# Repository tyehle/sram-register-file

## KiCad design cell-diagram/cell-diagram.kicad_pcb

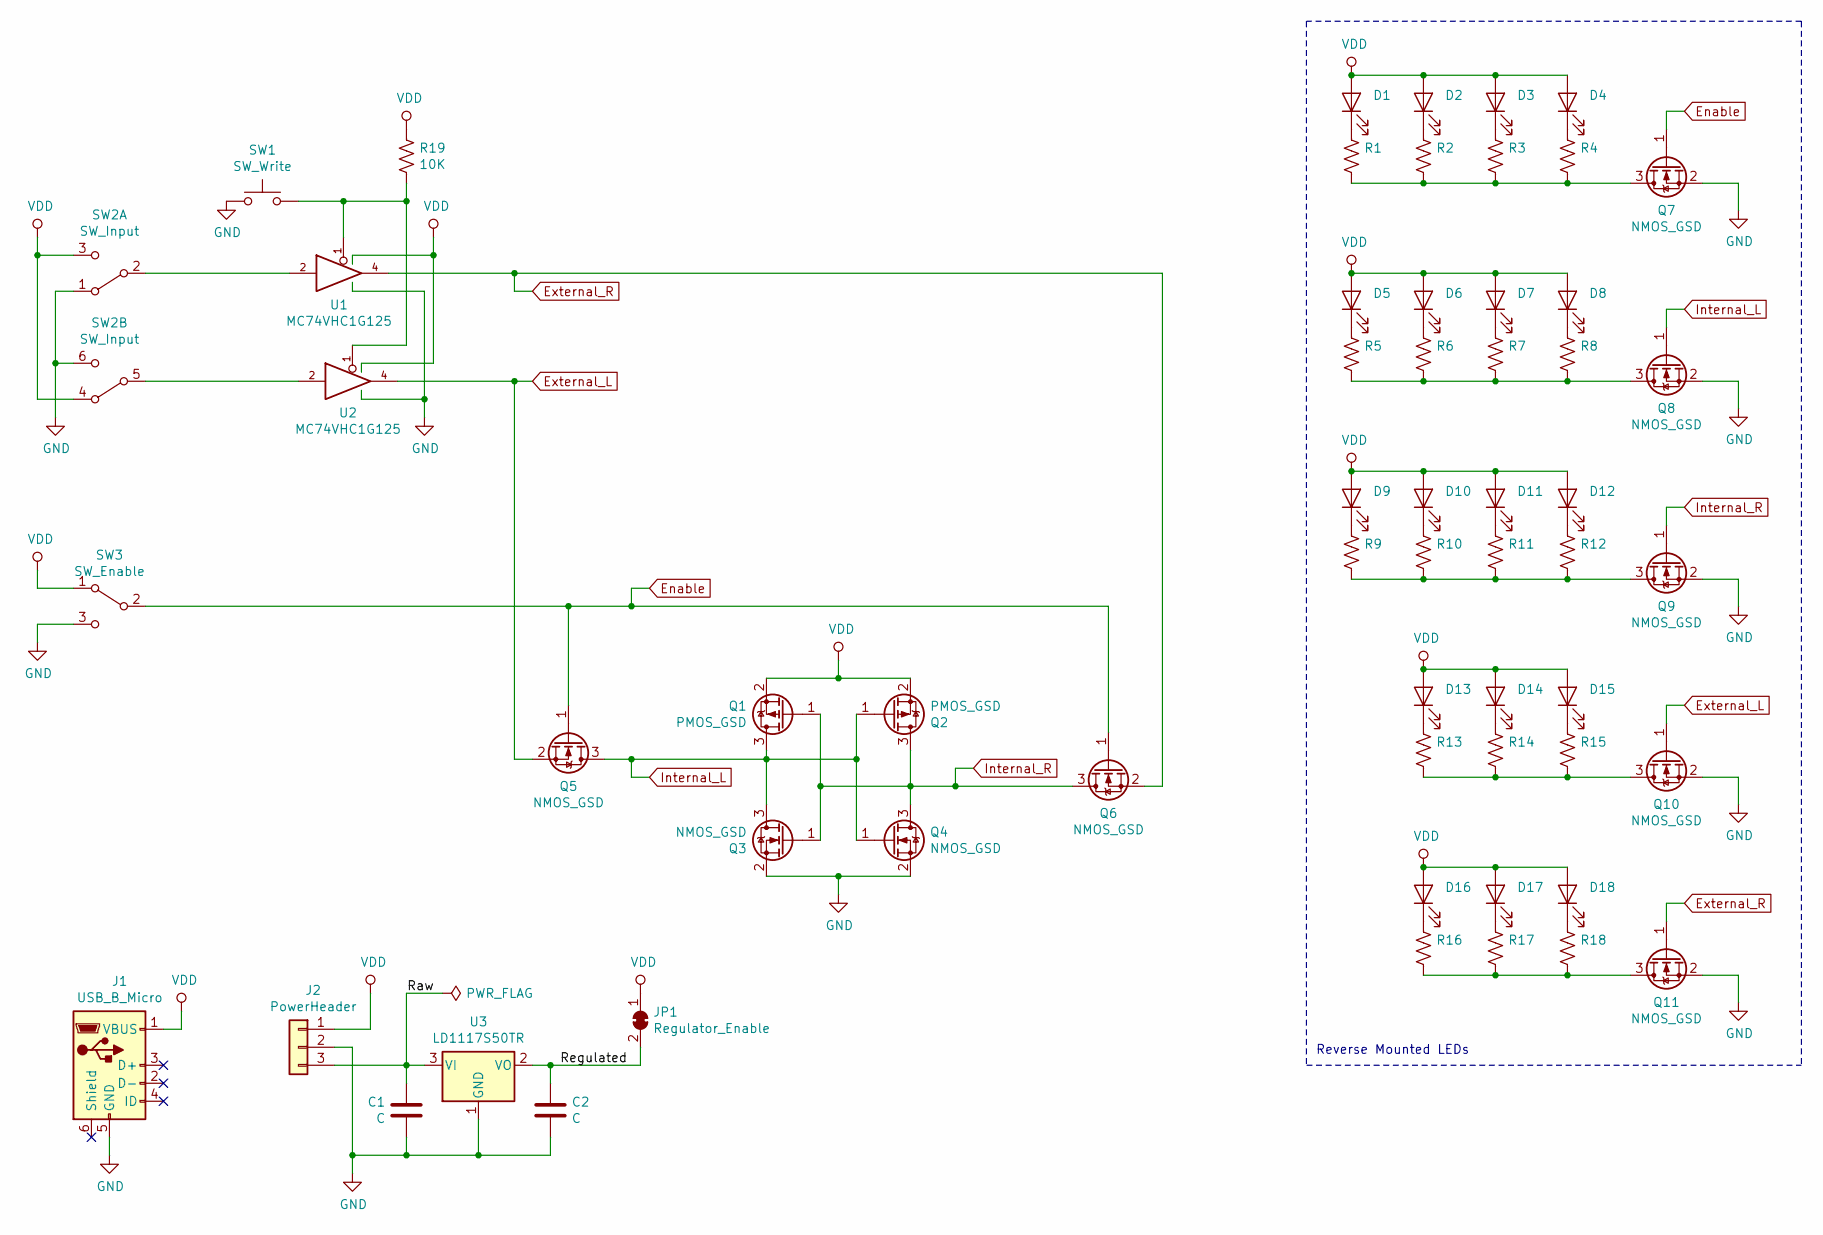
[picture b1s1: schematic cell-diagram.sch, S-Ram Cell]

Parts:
C1, C2: C; C_0805_2012Metric_Pad1.15x1.40mm_HandSolder
D1, D2, D3, D4, D5, D6, D7, D8, D9, D10, D11, D12, D13, D14, D15, D16, D17, D18: LED_1206_ReverseMountSquare1.5mm_HandSolder
J1: USB_B_Micro; USB_Micro-B_Molex-105017-0001
J2: PowerHeader; PowerHeader_P2.54mm
JP1: Regulator_Enable; SolderJumper-2_P1.3mm_Bridged_RoundedPad1.0x1.5mm
Q1, Q2: PMOS_GSD; SOT-23_Handsoldering
Q3, Q4, Q5, Q6, Q7, Q8, Q9, Q10, Q11: NMOS_GSD; SOT-23_Handsoldering
R1, R2, R3, R4, R5, R6, R7, R8, R9, R10, R11, R12, R13, R14, R15, R16, R17, R18: R_0805_2012Metric_Pad1.15x1.40mm_HandSolder
R19: 10K; R_0805_2012Metric_Pad1.15x1.40mm_HandSolder
SW1: SW_Write; SW_PUSH_6mm
SW2: SW_Input; Switch_DPDT_THT_CK
SW3: SW_Enable; Switch_DPDT_THT_CK
U1, U2: MC74VHC1G125; SOT-23-5
U3: LD1117S50TR; SOT-223-3_TabPin2

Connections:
/Raw: C1.1, J2.3, U3.3 (VI)
/Regulated: C2.1, JP1.2 (B), U3.2 (VO)
Enable: Q5.1 (G), Q6.1 (G), Q7.1 (G), SW3.2 (B)
External_L: Q5.2 (S), Q10.1 (G), U2.4
External_R: Q6.2 (S), Q11.1 (G), U1.4
GND: C1.2, C2.2, J1.5 (GND), J2.2, Q3.2 (S), Q4.2 (S), Q7.2 (S), Q8.2 (S), Q9.2 (S), Q10.2 (S), Q11.2 (S), SW1.1, SW2.1 (A), SW2.6 (C), SW3.3 (C), U1.3 (GND), U2.3 (GND), U3.1 (GND)
Internal_L: Q1.3 (D), Q2.1 (G), Q3.3 (D), Q4.1 (G), Q5.3 (D), Q8.1 (G)
Internal_R: Q1.1 (G), Q2.3 (D), Q3.1 (G), Q4.3 (D), Q6.3 (D), Q9.1 (G)
unnamed: D1.1 (K), R1.1
unnamed: D2.1 (K), R2.1
unnamed: D3.1 (K), R3.1
unnamed: D4.1 (K), R4.1
unnamed: D5.1 (K), R5.1
unnamed: D6.1 (K), R6.1
unnamed: D7.1 (K), R7.1
unnamed: D8.1 (K), R8.1
unnamed: D9.1 (K), R9.1
unnamed: D10.1 (K), R10.1
unnamed: D11.1 (K), R11.1
unnamed: D12.1 (K), R12.1
unnamed: D13.1 (K), R13.1
unnamed: D14.1 (K), R14.1
unnamed: D15.1 (K), R15.1
unnamed: D16.1 (K), R16.1
unnamed: D17.1 (K), R17.1
unnamed: D18.1 (K), R18.1
unnamed: Q7.3 (D), R1.2, R2.2, R3.2, R4.2
unnamed: Q8.3 (D), R5.2, R6.2, R7.2, R8.2
unnamed: Q9.3 (D), R9.2, R10.2, R11.2, R12.2
unnamed: Q10.3 (D), R13.2, R14.2, R15.2
unnamed: Q11.3 (D), R16.2, R17.2, R18.2
unnamed: R19.2, SW1.2, U1.1, U2.1
unnamed: SW2.2 (B), U1.2
unnamed: SW2.5 (B), U2.2
VCC: D1.2 (A), D2.2 (A), D3.2 (A), D4.2 (A), D5.2 (A), D6.2 (A), D7.2 (A), D8.2 (A), D9.2 (A), D10.2 (A), D11.2 (A), D12.2 (A), D13.2 (A), D14.2 (A), D15.2 (A), D16.2 (A), D17.2 (A), D18.2 (A), J1.1 (VBUS), J2.1, JP1.1 (A), Q1.2 (S), Q2.2 (S), R19.1, SW2.3 (C), SW2.4 (A), SW3.1 (A), U1.5 (VCC), U2.5 (VCC)

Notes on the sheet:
Reverse Mounted LEDs

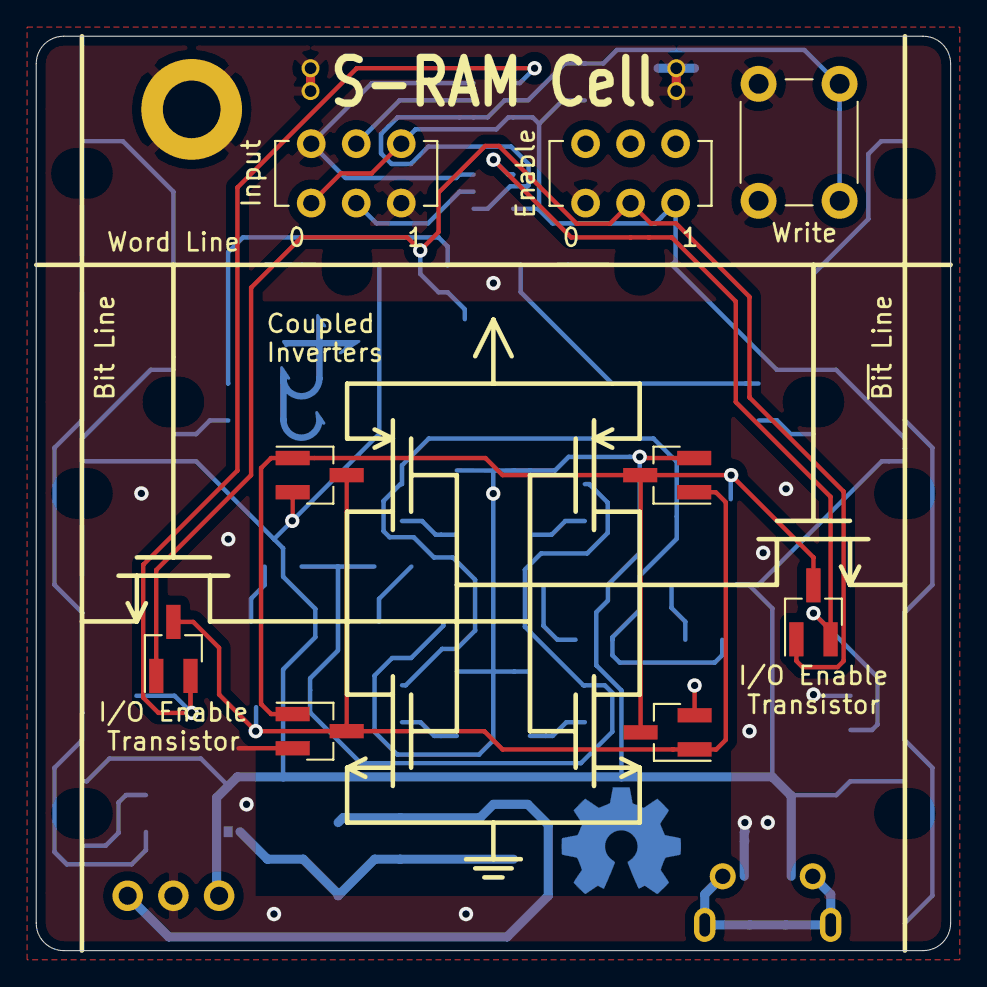
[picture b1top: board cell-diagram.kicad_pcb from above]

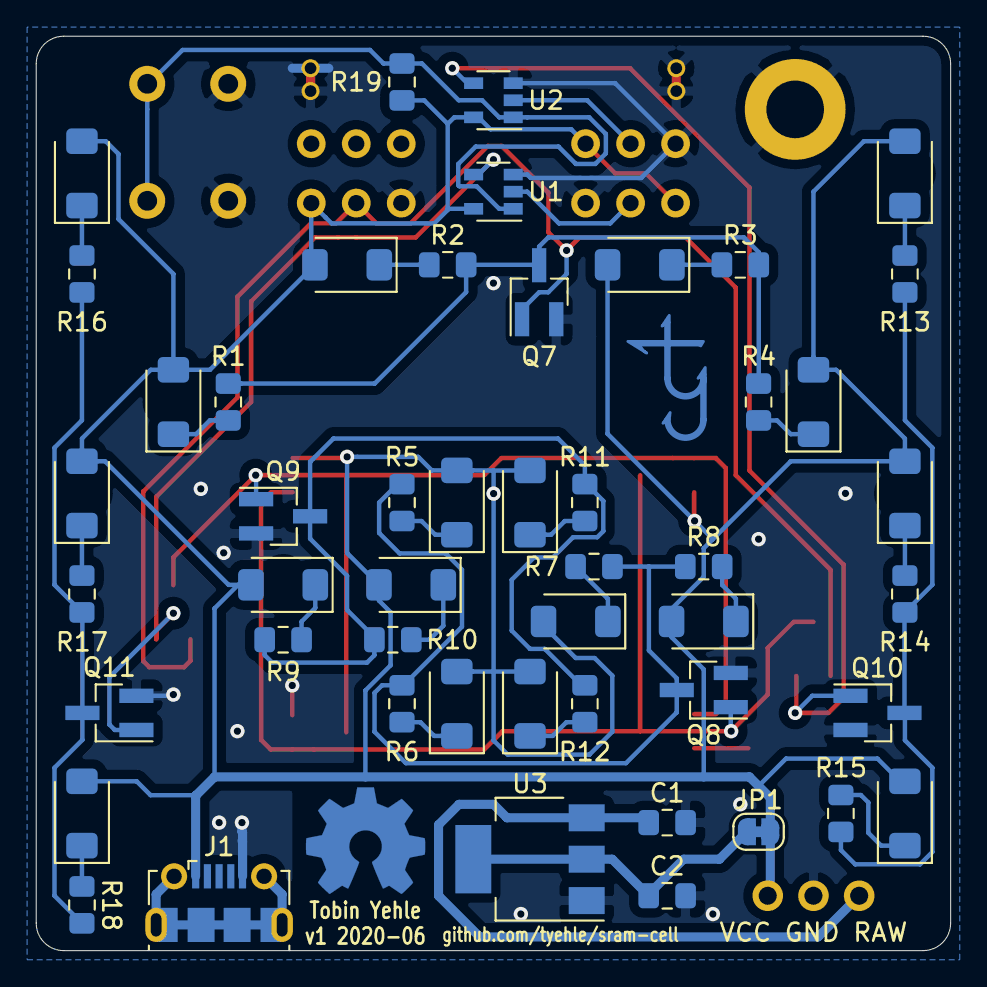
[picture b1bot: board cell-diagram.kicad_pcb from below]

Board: 2 copper layers, 50.8 x 50.8 mm, 59 parts (50 on the bottom side), 35 nets.

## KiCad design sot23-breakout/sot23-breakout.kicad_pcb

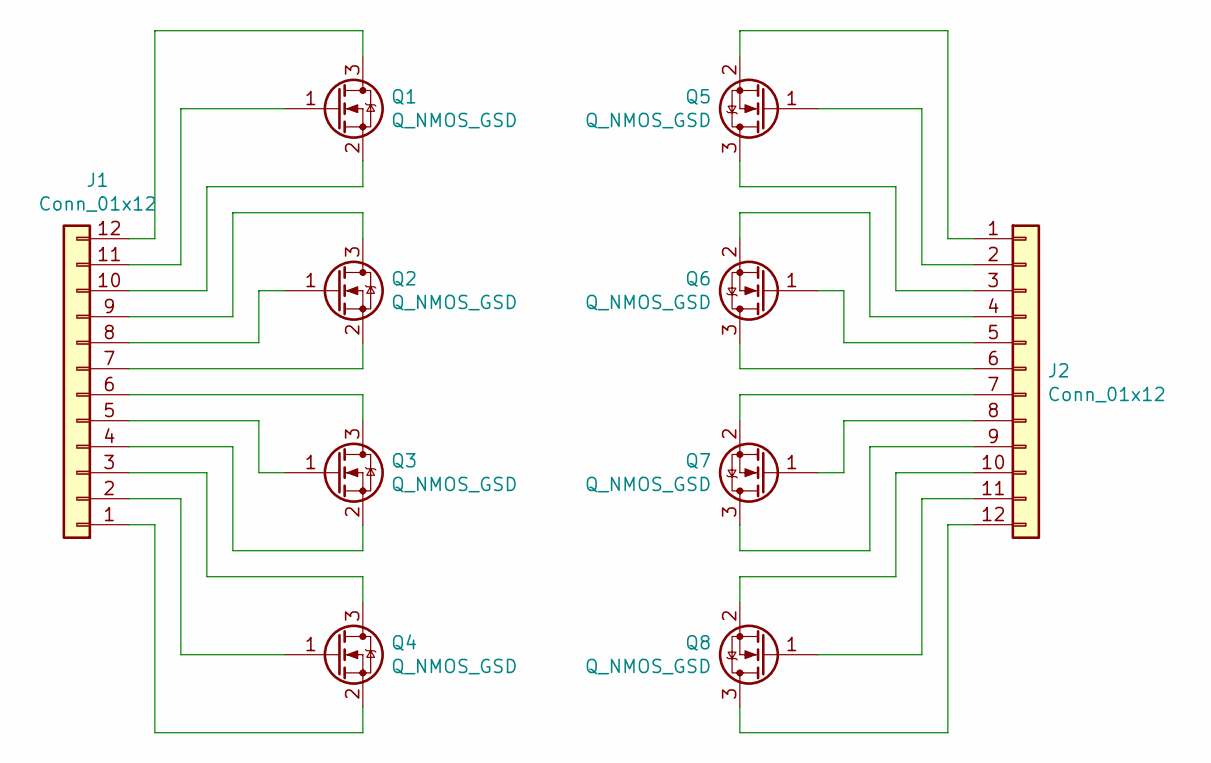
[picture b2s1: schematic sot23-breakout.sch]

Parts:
J1, J2: Conn_01x12; Header_1x12_P2.54mm
Q1, Q2, Q3, Q4, Q5, Q6, Q7, Q8: Q_NMOS_GSD; SOT-23_Handsoldering

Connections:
unnamed: J1.1, Q4.2 (S)
unnamed: J1.2, Q4.1 (G)
unnamed: J1.3, Q4.3 (D)
unnamed: J1.4, Q3.2 (S)
unnamed: J1.5, Q3.1 (G)
unnamed: J1.6, Q3.3 (D)
unnamed: J1.7, Q2.2 (S)
unnamed: J1.8, Q2.1 (G)
unnamed: J1.9, Q2.3 (D)
unnamed: J1.10, Q1.2 (S)
unnamed: J1.11, Q1.1 (G)
unnamed: J1.12, Q1.3 (D)
unnamed: J2.1, Q5.2 (S)
unnamed: J2.2, Q5.1 (G)
unnamed: J2.3, Q5.3 (D)
unnamed: J2.4, Q6.2 (S)
unnamed: J2.5, Q6.1 (G)
unnamed: J2.6, Q6.3 (D)
unnamed: J2.7, Q7.2 (S)
unnamed: J2.8, Q7.1 (G)
unnamed: J2.9, Q7.3 (D)
unnamed: J2.10, Q8.2 (S)
unnamed: J2.11, Q8.1 (G)
unnamed: J2.12, Q8.3 (D)

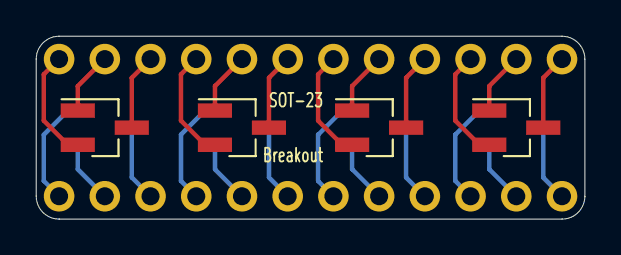
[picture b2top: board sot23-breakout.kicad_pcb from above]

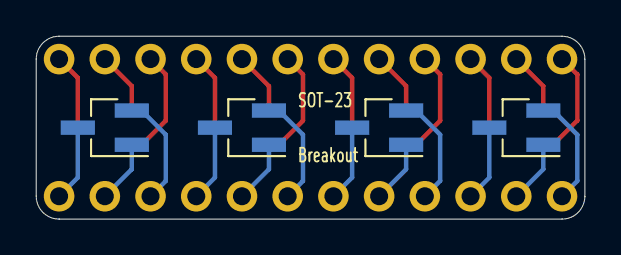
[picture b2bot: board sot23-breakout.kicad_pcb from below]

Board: 2 copper layers, 30.5 x 10.2 mm, 10 parts (4 on the bottom side), 24 nets.

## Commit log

2020-04-18 version 1
2020-04-18 move cell to a folder
2020-04-18 SOT-23 x 4 breakout board
2020-04-18 change SOT-23 breakout to have 8 chips
2020-05-02 initial falstad circuit simulation
2020-05-09 initial schematic
2020-05-09 basic work on the pcb diagram
2020-05-29 use a tristate buffer for the write bit lines in the falstad circuit
2020-06-01 finish routing
2020-06-01 add optional power regulation
2020-06-02 update falstad sim with the final design
2020-06-02 make some cosmetic improvements

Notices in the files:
cell-diagram/cell-diagram.sch:
CC BY-NC-SA
